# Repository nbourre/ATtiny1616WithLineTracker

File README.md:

# Introduction

TODO : Add content to file...
TODO : Add warning for the used RJ25 cable to jst connector

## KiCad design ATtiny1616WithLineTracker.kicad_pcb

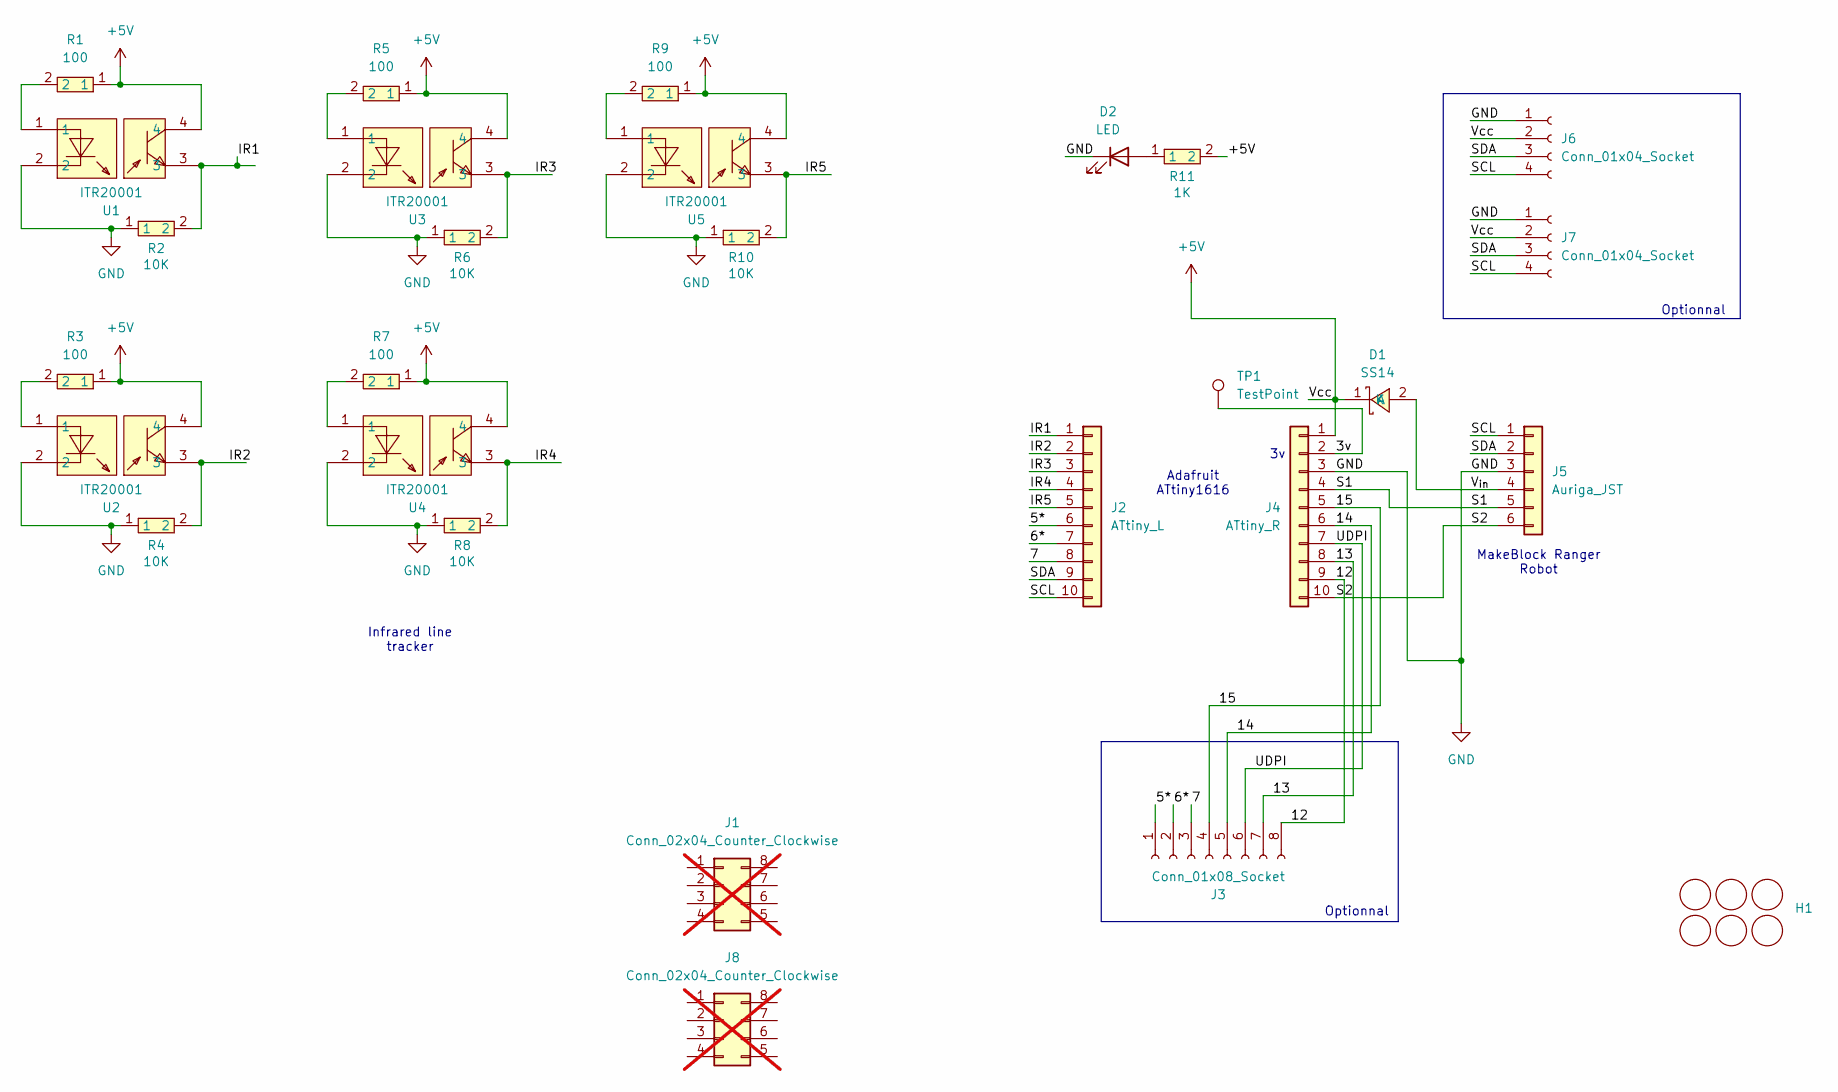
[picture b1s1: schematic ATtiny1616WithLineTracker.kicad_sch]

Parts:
D1: SS14; SMA_L4.2-W2.6-LS5.3-RD; LCSC Part C2480
D2: LED; LED_0603_1608Metric; LCSC C2286
H1: MountingHole_4.3mm_M4_Pad_TopBottom_MakeBlock
J1, J8: Conn_02x04_Counter_Clockwise; PinHeader_2x04_P2.54mm_Vertical; not fitted
J2: ATtiny_L; PinSocket_1x10_P2.54mm_Vertical; LCSC C2897373
J3: Conn_01x08_Socket; PinSocket_1x08_P2.54mm_Vertical; LCSC C27438
J4: ATtiny_R; PinSocket_1x10_P2.54mm_Vertical; LCSC C2897373
J5: Auriga_JST; JST_XH_S6B-XH-A-1_1x06_P2.50mm_Horizontal; LCSC C157919
J6, J7: Conn_01x04_Socket; PinSocket_1x04_P2.54mm_GVSCLSDC; LCSC C2718488
R1, R3, R5, R7, R9: 100; R0603; LCSC Part C105588
R2, R4, R6, R8, R10: 10K; R0603; LCSC Part C25804
R11: 1K; R0603; LCSC Part C21190
TP1: TestPoint; PinHeader_1x01_P1.00mm_Vertical
U1, U2, U3, U4, U5: ITR20001; OPTO-TH_DY-ITR20001; LCSC Part C459138

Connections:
+5V: D1.1 (K), J4.1 (Vin), J6.2, J7.2, R1.1, R3.1, R5.1, R7.1, R9.1, R11.2, U1.4, U2.4, U3.4, U4.4, U5.4
/3v: J4.2 (3v), TP1.1
/5*: J2.6 (Pin_5), J3.1
/6*: J2.7 (RXD), J3.2
/7: J2.8 (TXD), J3.3
/12: J3.8, J4.9 (Pin_12)
/13: J3.7, J4.8 (Pin_13)
/14: J3.5, J4.6 (Pin_14)
/15: J3.4, J4.5 (Pin_15)
/IR1: J2.1 (Pin_0), R2.2, U1.3
/IR2: J2.2 (Pin_1), R4.2, U2.3
/IR3: J2.3 (Pin_2), R6.2, U3.3
/IR4: J2.4 (Pin_3), R8.2, U4.3
/IR5: J2.5 (Pin_4), R10.2, U5.3
/S1: J4.4 (Pin_16), J5.5 (S1)
/S2: J4.10 (Pin_11), J5.6 (S2)
/SCL: J2.10 (SCL), J5.1 (SCL), J6.4, J7.4
/SDA: J2.9 (SDA), J5.2 (SDA), J6.3, J7.3
/UDPI: J3.6, J4.7 (UPDI)
/V_{in}: D1.2 (A), J5.4 (PWR_B)
GND: D2.1 (K), J4.3 (GND), J5.3 (PWR_A), J6.1, J7.1, R2.1, R4.1, R6.1, R8.1, R10.1, U1.2, U2.2, U3.2, U4.2, U5.2
unnamed: D2.2 (A), R11.1
unnamed: R1.2, U1.1
unnamed: R3.2, U2.1
unnamed: R5.2, U3.1
unnamed: R7.2, U4.1
unnamed: R9.2, U5.1

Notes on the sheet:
Infrared line tracker
Optionnal
MakeBlock Ranger Robot
Adafruit ATtiny1616

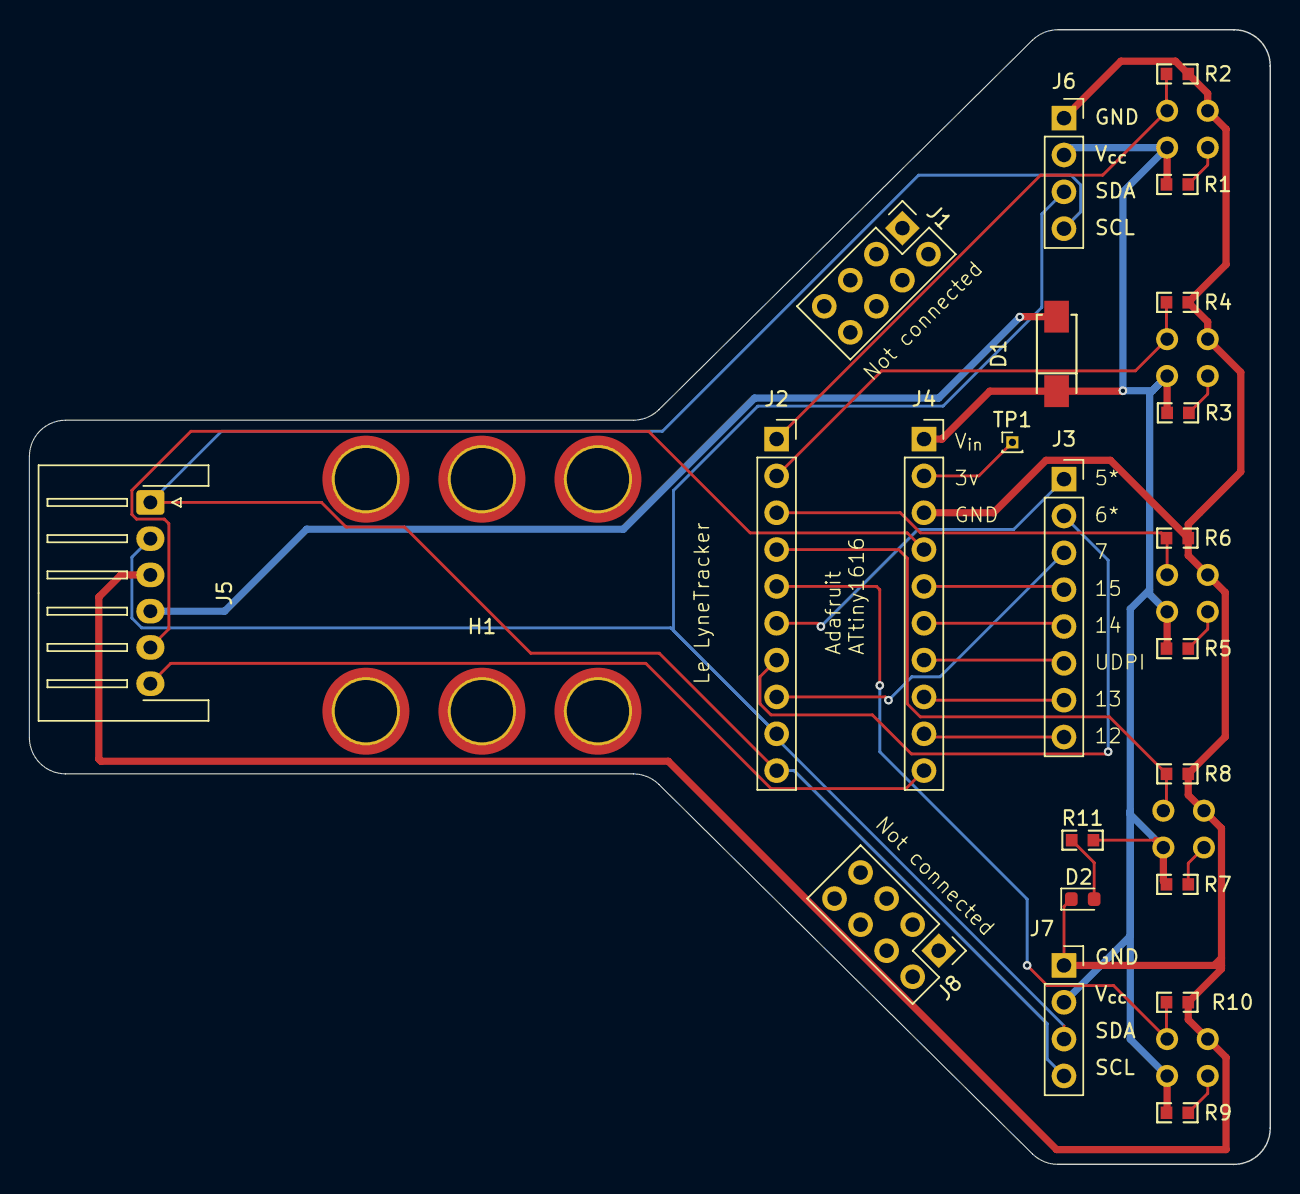
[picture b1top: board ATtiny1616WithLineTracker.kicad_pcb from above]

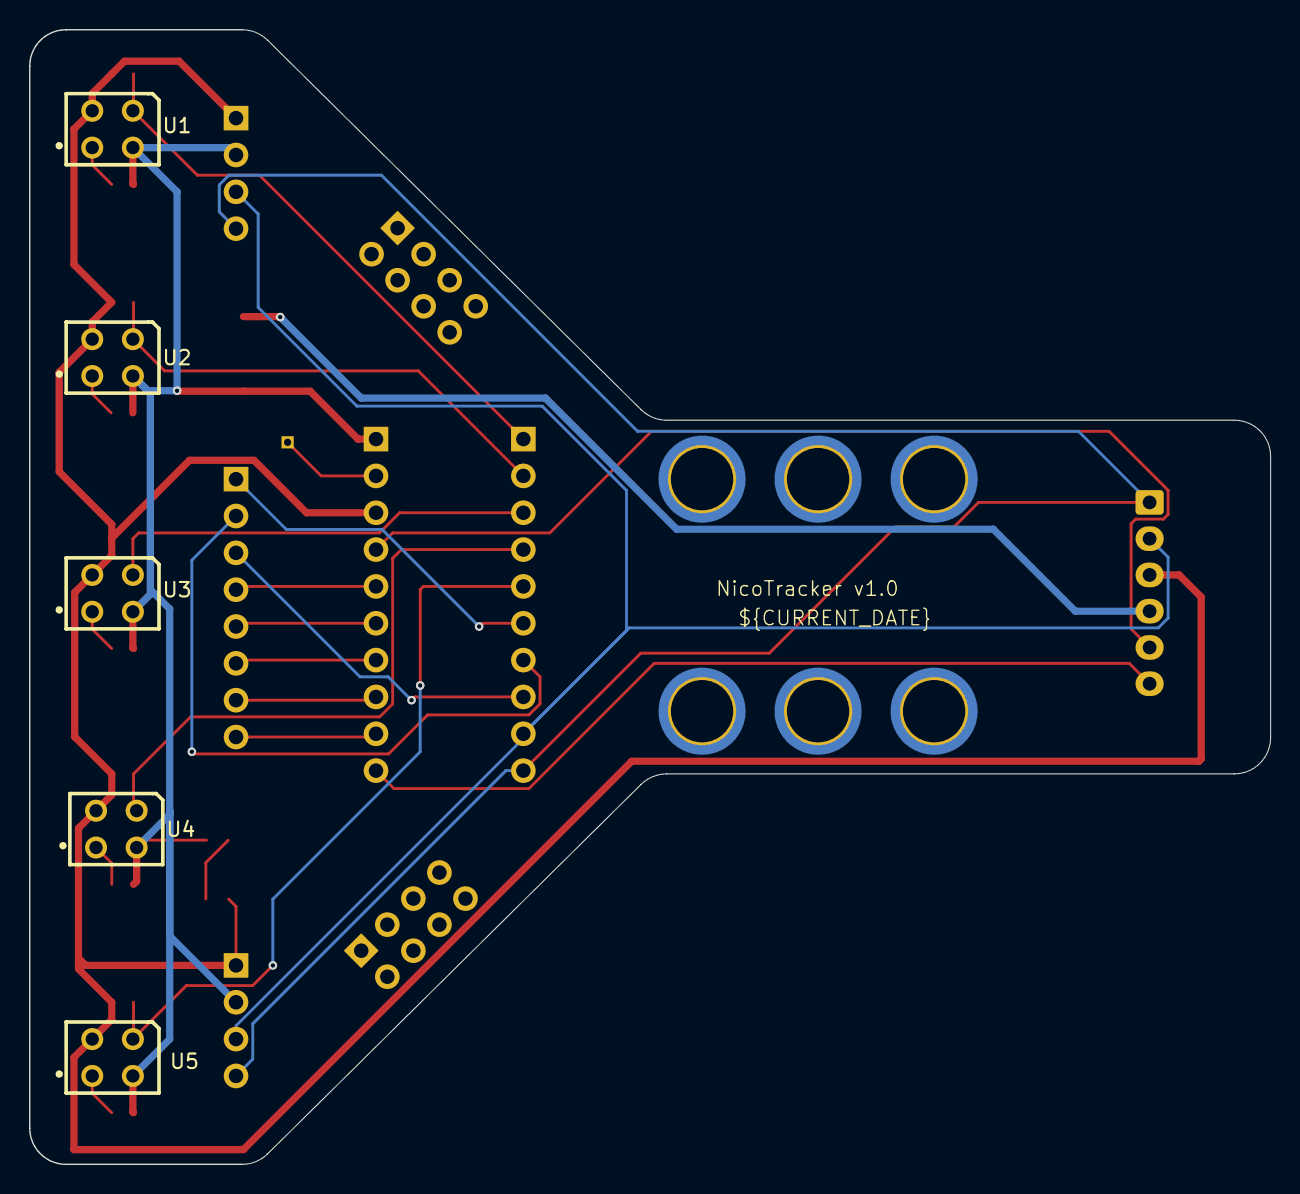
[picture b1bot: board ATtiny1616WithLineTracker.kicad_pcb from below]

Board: 2 copper layers, 85.5 x 78.2 mm, 28 parts (5 on the bottom side), 27 nets.

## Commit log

2024-09-28 Added pictures
2024-09-28 Added a TODO
2024-10-03 Fix SDA-SCL silk markings
2025-08-21 Ajout de note pour améliorations futures
